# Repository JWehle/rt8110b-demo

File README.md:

# rt8110b-demo
Demo board for the RT8110B buck converter controller.

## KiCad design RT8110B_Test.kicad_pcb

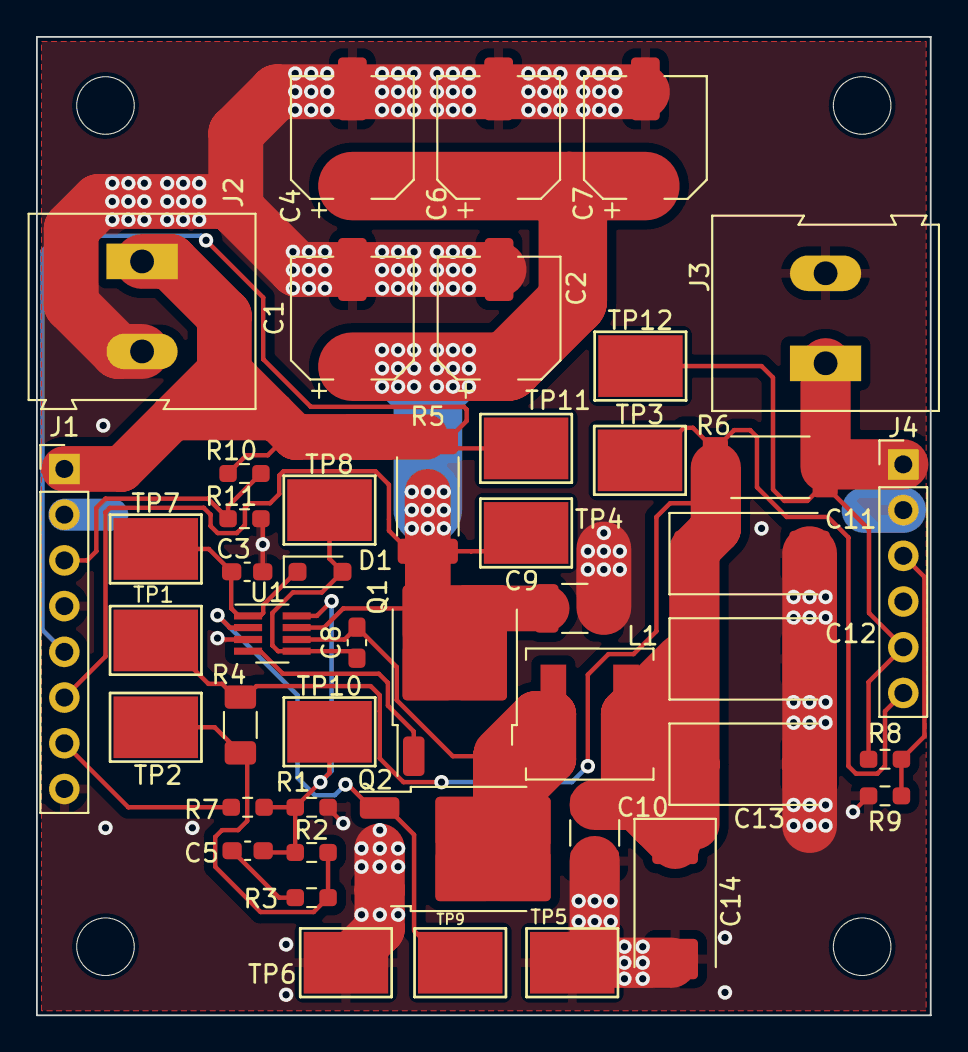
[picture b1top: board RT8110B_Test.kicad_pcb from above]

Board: 2 copper layers, 49.7 x 54.4 mm, 50 parts (0 on the bottom side), 16 nets.

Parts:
C1, C2, C4, C6, C7: 100uF; CP_Elec_6.3x5.4_Nichicon
C3: 1uF; C_0603_1608Metric_Pad1.08x0.95mm_HandSolder
C5: 20pF; C_0603_1608Metric_Pad1.08x0.95mm_HandSolder
C8: 0.1uF; C_0603_1608Metric_Pad1.08x0.95mm_HandSolder
C9, C10: 22uF; C_1210_3225Metric_Pad1.33x2.70mm_HandSolder
C11, C12, C13, C14: 100uF; CP_EIA-7343-43_Kemet-X_Pad2.25x2.55mm_HandSolder
D1: 1N5819WS; D_SOD-323_HandSoldering
H1, H2, H3, H4: MountingHole; MountingHole_3.2mm_M3
J1: Conn_01x08; PinHeader_1x08_P2.54mm_Vertical
J2, J3: Screw_Terminal_01x02; TerminalBlock_Altech_AK300-2_P5.00mm
J4: Conn_01x06; PinHeader_1x06_P2.54mm_Vertical
L1: 4.7uH; L_Coilcraft_XAL6060-XXX
Q1, Q2: QM6006D; TO-252-2
R1, R8, R9, R10, R11: 10k; R_0603_1608Metric_Pad0.98x0.95mm_HandSolder
R2, R3, R7: 20k; R_0603_1608Metric_Pad0.98x0.95mm_HandSolder
R4: 20; R_1206_3216Metric_Pad1.30x1.75mm_HandSolder
R5, R6: 10m; R_2512_6332Metric_Pad1.40x3.35mm_HandSolder
TP1, TP2, TP3, TP4, TP5, TP6, TP7, TP8, TP9, TP10, TP11, TP12: 5016; TestPoint_Keystone_5016_Compact
U1: RT8110BGJ8; SOT-23-8_Handsoldering

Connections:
GND: C1.2, C2.2, C3.2, C4.2, C6.2, C7.2, C9.2, C10.2, C11.2, C12.2, C13.2, C14.2, J1.2, J1.4, J1.8, J2.2, J3.2, J4.2, J4.4, Q2.3 (S), R1.2, R9.2, R11.2, TP5.1, TP6.1, U1.3 (GND)
unnamed: C5.2, R3.1
unnamed: C8.1, D1.2 (A), TP8.1, U1.5 (BOOT)
unnamed: C3.1, D1.1 (K), TP7.1, U1.1 (VCC)
unnamed: J1.1, J1.5, J2.1, R5.1, R10.1, TP11.1
unnamed: J1.3, R10.2, R11.1
unnamed: C1.1, C2.1, C4.1, C6.1, C7.1, C9.1, J1.6, Q1.2 (D), R5.2, TP4.1, U1.7 (VIN)
unnamed: J1.7, R7.1
unnamed: J3.1, J4.1, J4.5, R6.2, R8.1, TP12.1
unnamed: J4.3, R8.2, R9.1
unnamed: C10.1, C11.1, C12.1, C13.1, C14.1, J4.6, L1.2, R4.2, R6.1, TP1.1, TP3.1
unnamed: Q1.1 (G), U1.4 (UGATE)
unnamed: C8.2, L1.1, Q1.3 (S), Q2.2 (D), U1.6 (PHASE)
unnamed: Q2.1 (G), TP9.1, U1.2 (LGATE)
unnamed: R2.2, R3.2, R4.1, TP2.1
unnamed: C5.1, R1.1, R2.1, R7.2, TP10.1, U1.8 (FB)
